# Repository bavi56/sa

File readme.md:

# Servisní analyzátor s arduino Nano

* 8x 24V digitalni vstup
* 3x analogový vstup pro SCT013

## Firmware

[arduino Nano](./sa.ino)

Odkomentovat pro čitelný výpis do serial monitoru:
```c++
#define DEBUG
```

Seznam součástek [zde](./eagle/partlist.txt).

## Zobrazení

* ### processing [zde](./processing/sa_java.pde)

* ### python [zde](./sa.pyw) (potřeba stáhnout modul [pygraf](https://github.com/blindp/pygraf) a mít nainstalovaný tkinter)

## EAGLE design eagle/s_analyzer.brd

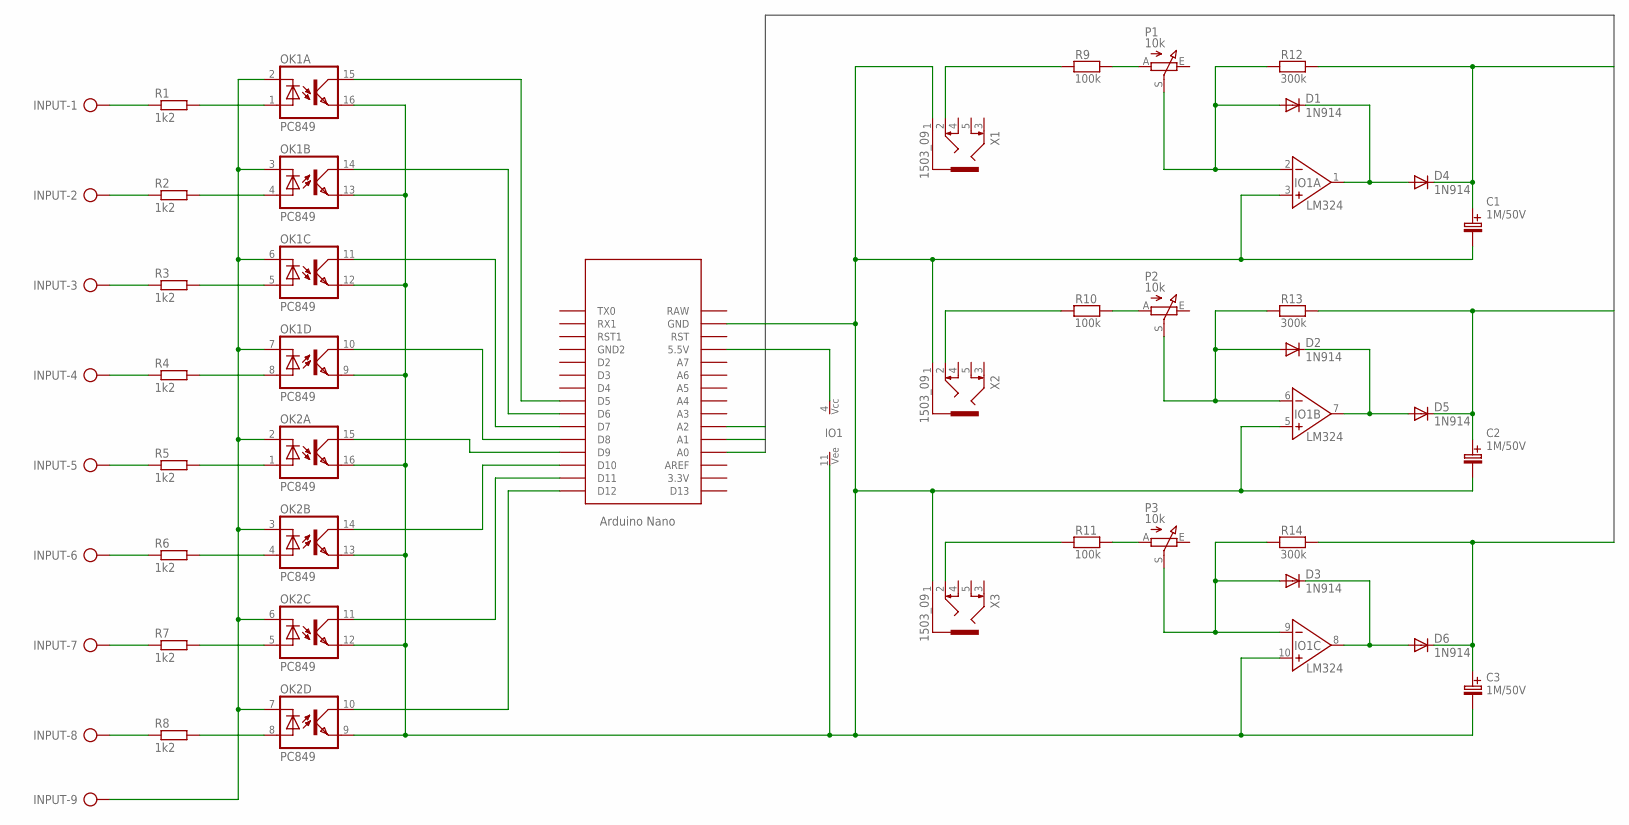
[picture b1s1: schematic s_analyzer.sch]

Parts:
C1, C2, C3: 1M/50V; C_EL_2
D1, D2, D3, D4, D5, D6: 1N914; DO35-7
INPUT: AK500/9
IO1: LM324; DIL14
OK1, OK2: PC849; DIL16
P1, P2, P3: 10k; PT10V
R1, R2, R3, R4, R5, R6, R7, R8: 1k2; 0204/5
R9, R10, R11: 100k; R_7,5
R12, R13, R14: 300k; R_7,5
U$1: NANO
X1, X2, X3: 1503_09

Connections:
A0: C1.C+ (C_EL+), D4.C, R12.2, U$1.A0
A1: C2.C+ (C_EL+), D5.C, R13.2, U$1.A1
A2: C3.C+ (C_EL+), D6.C, R14.2, U$1.A2
unnamed: INPUT.1, R1.1
unnamed: OK1.1 (A), R1.2
unnamed: INPUT.2, R2.1
unnamed: OK1.4 (A), R2.2
unnamed: INPUT.3, R3.1
unnamed: OK1.5 (A), R3.2
unnamed: INPUT.4, R4.1
unnamed: OK1.8 (A), R4.2
unnamed: INPUT.5, R5.1
unnamed: OK2.1 (A), R5.2
unnamed: INPUT.6, R6.1
unnamed: OK2.4 (A), R6.2
unnamed: INPUT.7, R7.1
unnamed: OK2.5 (A), R7.2
unnamed: INPUT.8, R8.1
unnamed: OK2.8 (A), R8.2
unnamed: INPUT.9, OK1.2 (C), OK1.3 (C), OK1.6 (C), OK1.7 (C), OK2.2 (C), OK2.3 (C), OK2.6 (C), OK2.7 (C)
unnamed: IO1.4 (VCC), U$1.5V (5.5V)
unnamed: OK2.10 (COL), U$1.D12
unnamed: OK2.11 (COL), U$1.D11
unnamed: OK2.14 (COL), U$1.D10
unnamed: OK2.15 (COL), U$1.D9
unnamed: OK1.10 (COL), U$1.D8
unnamed: OK1.11 (COL), U$1.D7
unnamed: OK1.14 (COL), U$1.D6
unnamed: OK1.15 (COL), U$1.D5
unnamed: D1.A, IO1.2 (IN-), P1.S, R12.1
unnamed: P1.A, R9.2
unnamed: D1.C, D4.A, IO1.1 (VYSTUP)
unnamed: R11.1, X3.2
unnamed: P2.A, R10.2
unnamed: D2.A, IO1.6 (IN-), P2.S, R13.1
unnamed: D2.C, D5.A, IO1.7 (VYSTUP)
unnamed: R10.1, X2.2
unnamed: P3.A, R11.2
unnamed: D3.A, IO1.9 (IN-), P3.S, R14.1
unnamed: D3.C, D6.A, IO1.8 (VYSTUP)
unnamed: R9.1, X1.2
unnamed: C1.C- (C_EL-), C2.C- (C_EL-), C3.C- (C_EL-), IO1.3 (NEIN+), IO1.5 (NEIN+), IO1.10 (NEIN+), IO1.11 (VEE), OK1.9 (EMI), OK1.12 (EMI), OK1.13 (EMI), OK1.16 (EMI), OK2.9 (EMI), OK2.12 (EMI), OK2.13 (EMI), OK2.16 (EMI), U$1.GND, X1.1, X2.1, X3.1

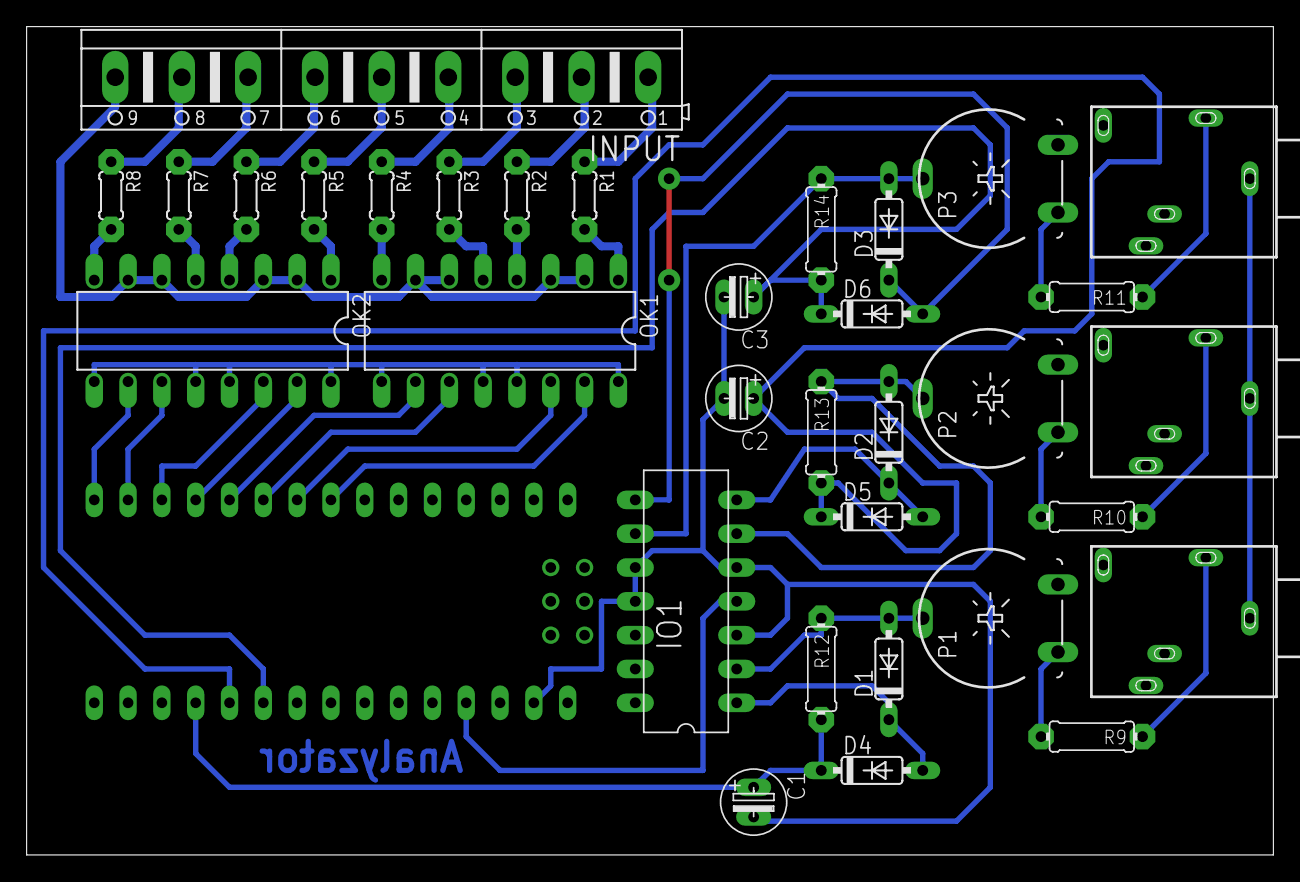
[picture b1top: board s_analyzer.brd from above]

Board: 2 copper layers, 93.6 x 62.2 mm, 34 parts (0 on the bottom side), 42 nets.

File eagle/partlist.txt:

Partlist

Exported from s_analyzer.sch at 04.02.18 13:12

EAGLE Version 7.6.0 Copyright (c) 1988-2016 CadSoft

Assembly variant: 

Part     Value          Device       Package  Library       Sheet

C1       1M/50V         1M/50V       C_EL_2   #PaJa_C-el_2  1
C2       1M/50V         1M/50V       C_EL_2   #PaJa_C-el_2  1
C3       1M/50V         1M/50V       C_EL_2   #PaJa_C-el_2  1
D1       1N914          1N4148DO35-7 DO35-7   diode         1
D2       1N914          1N4148DO35-7 DO35-7   diode         1
D3       1N914          1N4148DO35-7 DO35-7   diode         1
D4       1N914          1N4148DO35-7 DO35-7   diode         1
D5       1N914          1N4148DO35-7 DO35-7   diode         1
D6       1N914          1N4148DO35-7 DO35-7   diode         1
INPUT                   AK500/9      AK500/9  #Svorkovnice  1
IO1      LM324          LM324        DIL14    #PaJa_31      1
OK1      PC849          PC849        DIL16    optocoupler   1
OK2      PC849          PC849        DIL16    optocoupler   1
P1       10k            TRIMRPT10V   PT10V    #Trimry       1
P2       10k            TRIMRPT10V   PT10V    #Trimry       1
P3       10k            TRIMRPT10V   PT10V    #Trimry       1
R1       1k2            R-EU_0204/5  0204/5   #Odpory       1
R2       1k2            R-EU_0204/5  0204/5   #Odpory       1
R3       1k2            R-EU_0204/5  0204/5   #Odpory       1
R4       1k2            R-EU_0204/5  0204/5   #Odpory       1
R5       1k2            R-EU_0204/5  0204/5   #Odpory       1
R6       1k2            R-EU_0204/5  0204/5   #Odpory       1
R7       1k2            R-EU_0204/5  0204/5   #Odpory       1
R8       1k2            R-EU_0204/5  0204/5   #Odpory       1
R9       100k           330K         R_7,5    #PaJa_R       1
R10      100k           330K         R_7,5    #PaJa_R       1
R11      100k           330K         R_7,5    #PaJa_R       1
R12      300k           100K         R_7,5    #PaJa_R       1
R13      300k           100K         R_7,5    #PaJa_R       1
R14      300k           100K         R_7,5    #PaJa_R       1
U$1      NANO           NANO         NANO     Arduino-clone 1
X1       1503_09        1503_09      1503_09  con-lumberg   1
X2       1503_09        1503_09      1503_09  con-lumberg   1
X3       1503_09        1503_09      1503_09  con-lumberg   1

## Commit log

2018-02-04 init commit
2018-02-05 readme.md
2018-02-05 add sa.pyw
2018-02-05 edit readme

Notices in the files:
parts and their libraries:
Copyright (C) Vlada 2004-2005
Copyright (C) PaJa 2001-2014
Copyright (C) PaJa 2003-2009
